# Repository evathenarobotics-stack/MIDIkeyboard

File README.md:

# MIDIkeyboard
Created an MIDI keyboard through KiCad using a PCB. 

This project took a lot of time and effort to complete since I had little knowledge regarding PCBs and schematics.

I started with drawing a schematic of my components using a Waveshare ESP32-S3-Zero microcontroller and other components.

Later, I turned the schematic into a PCB and added keys to the board and wires the components together to finish it.

- 1 × Waveshare ESP32-S3-Zero microcontroller
- 7 × Capacitive touch keys
- 1 × 7-pin connector
- 3 × Push buttons
- 1 × Rotary encoder
- 2 × Potentiometers/sliders
- 3 × SK6812MINI-E RGB LEDs

It was a very tough process, but I learned a lot about PCB.

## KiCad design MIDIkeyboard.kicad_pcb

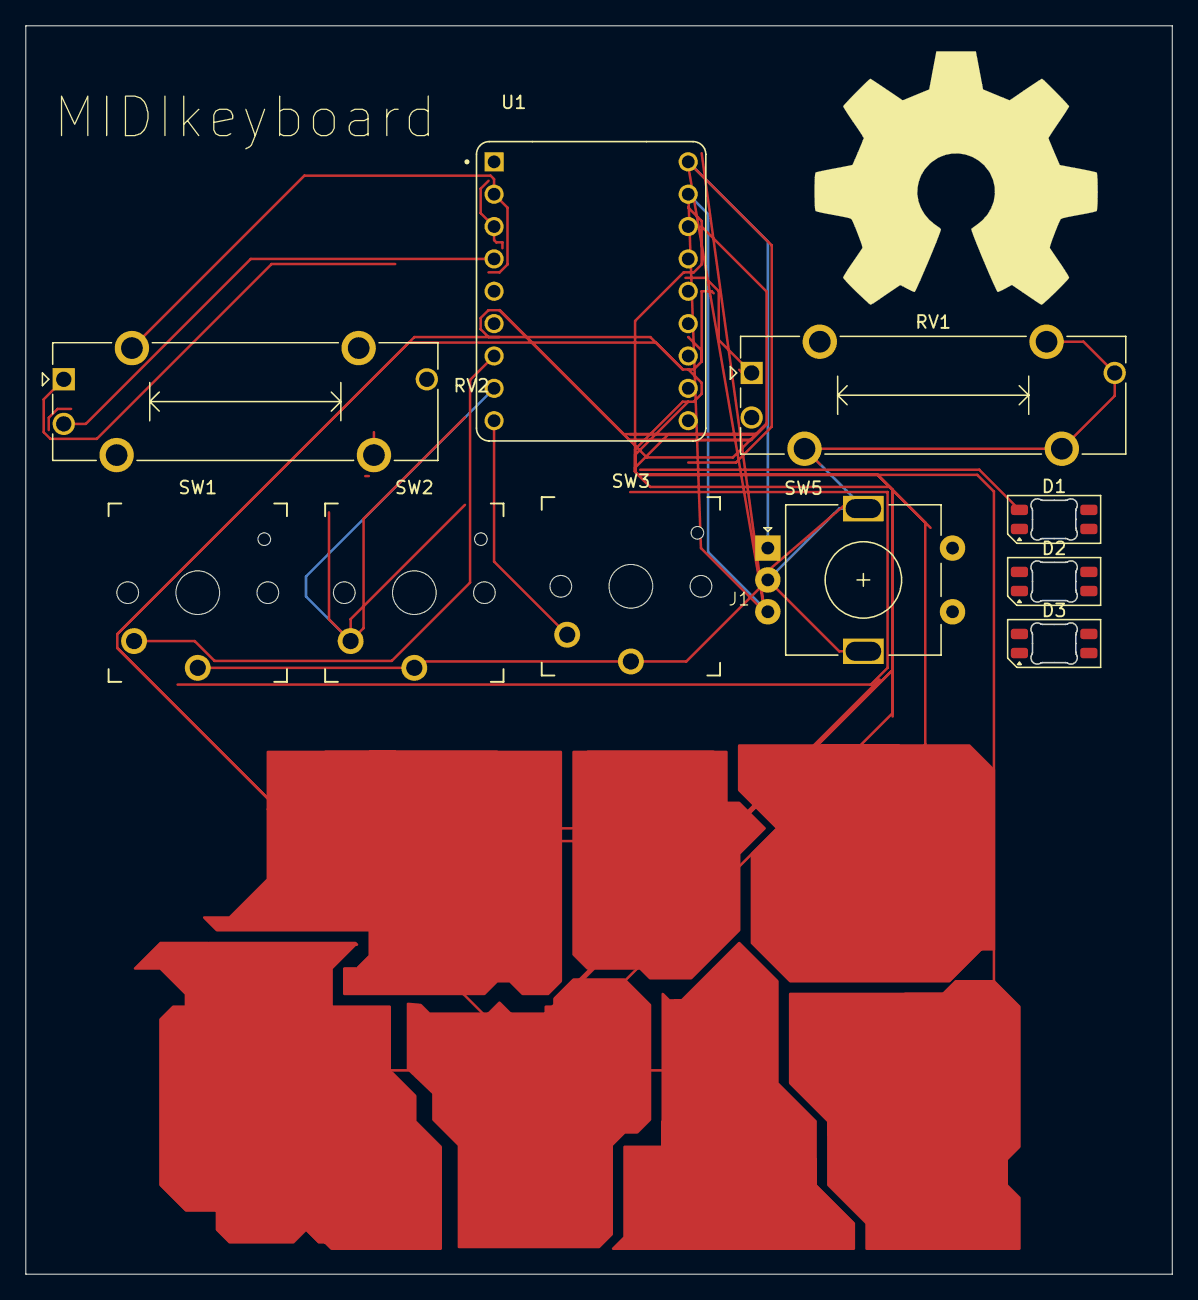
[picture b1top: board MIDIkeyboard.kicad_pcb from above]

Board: 2 copper layers, 90.0 x 98.0 mm, 11 parts (0 on the bottom side), 14 nets.

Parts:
D1, D2, D3: SK6812MINI-E; LED_SK6812MINI-E_3.2x2.8mm_P1.5mm_ReverseMount
J1: Capacitive Touch Buttons; Capacitive Keys
RV1, RV2: Slider; Potentiometer_Bourns_PTA1543_Single_Slide
SW1, SW2, SW3: SW_Push; Kailh Choc Low-Profile Switches
SW5: RotaryEncoder_Switch_MP; RotaryEncoder_Alps_EC11E-Switch_Vertical_H20mm
U1: Waveshare ESP32-S3-ZERO; Waveshare ESP32-S3-Zero

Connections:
+3V3: RV1.1, RV2.1, U1.3V3 (3V3(OUT))
/ENC1_A: SW5.A, U1.TX
/ENC1_B: SW5.B, U1.RX
/LED: D1.2 (DIN), U1.3 (GP3)
/SLIDE1: RV1.2, U1.2 (GP2)
/SLIDE2: RV2.2, U1.1 (GP1)
/SWITCH1: SW1.2, U1.4 (GP4)
/SWITCH2: SW2.2, U1.5 (GP5)
/SWITCH3: SW3.2, U1.6 (GP6)
GND: RV1.3, RV1.MP (MountPin), RV2.3, RV2.MP (MountPin), SW1.1, SW2.1, SW3.1, SW5.C, SW5.MP, U1.GND
unnamed: D1.4 (DOUT), D2.2 (DIN)
unnamed: D1.3 (VDD), D2.3 (VDD), D3.3 (VDD)
unnamed: D1.1 (VSS), D2.1 (VSS), D3.1 (VSS)
unnamed: D2.4 (DOUT), D3.2 (DIN)
